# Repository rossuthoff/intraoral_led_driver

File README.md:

# intraoral led driver
Switching boost LED driver based on the Linear Technology [LT3478-1](http://www.analog.com/en/products/power-management/led-driver-ic/buck-boost-led-drivers/lt3478.html) chip. This LED driver is used for the oral cancer screening device described in [1]. 

## related repositories
This design requires the footprints found in the [kicad_footprints](https://github.com/rossuthoff/kicad_footprints) repository. Make sure the library and .mod files are added to your folder search locations. This board utilizes the [ytai/IOIO](https://github.com/ytai/ioio) microcontroller (MCU). Other microcontrollers that can send 3.3 V signals and control an I2C interface may be used. 

## general use
### power supply
LED driver is used in boost mode. The battery voltage must be less than the voltage drop across each individual LED string. Connector J5 supplies power to the MCU.

### led strings
Connect the LED strings to A+/A- and B+/B- connections. The LED string to be illuminated is controlled through a 3.3V signal to the sA or sB pins. The applied current is controlled through a Analog Devices [AD5247](http://www.analog.com/en/products/digital-to-analog-converters/digital-potentiometers/ad5247.html) digital potentiometer with an I2C interface.

# references
[1] Uthoff, R. D. et al. Development of a dual-modality, dual-view smartphone-based imaging system for oral cancer detection. in Proc. SPIE 10486, Design and Quality for Biomedical Technologies XI 10486, 104860V-10486–7 (SPIE, 2018).

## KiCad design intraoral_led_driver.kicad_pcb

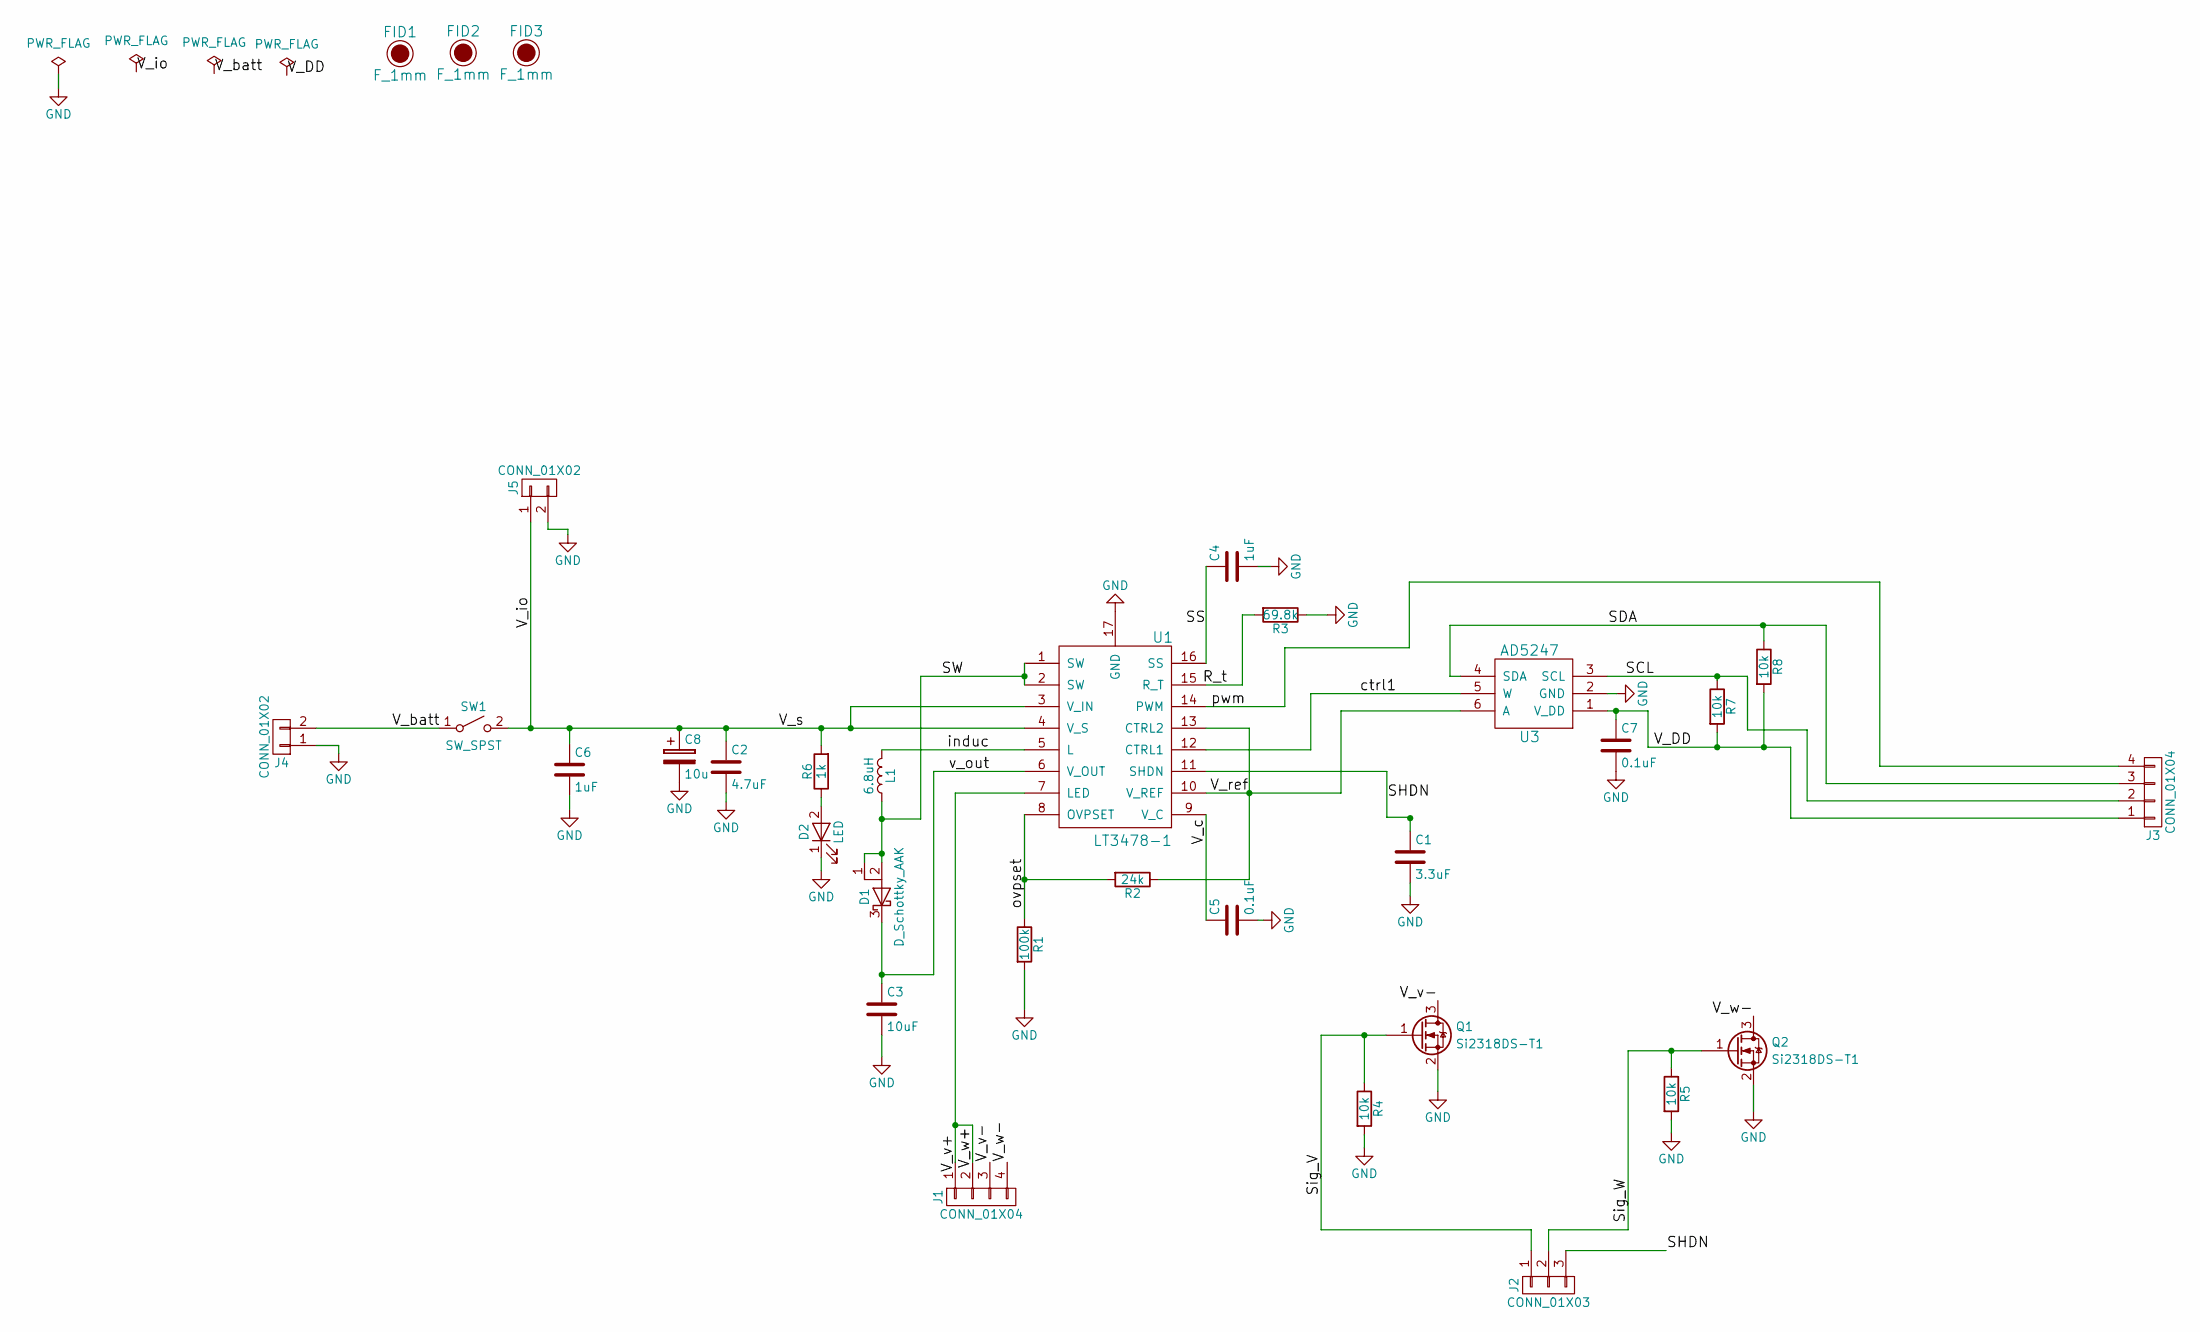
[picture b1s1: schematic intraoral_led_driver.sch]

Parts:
C1: 3.3uF; C_0603
C2: 4.7uF; C_1206
C3: 10uF; C_1812
C4, C6: 1uF; C_0603
C5, C7: 0.1uF; C_0603
C8: 10u; CP_Tantalum_Case-A_EIA-3216-18_Reflow
D1: D_Schottky_AAK; D_PowerDI-5
D2: LED; LED_0603
FID1, FID2, FID3: F_1mm; Fiducial_1mm_Dia_2mm_Outer_CopperTop
J1, J3: CONN_01X04; JST_PH_S4B-PH-SM4-TB_04x2.00mm_Angled
J2: CONN_01X03; JST_PH_S3B-PH-SM4-TB_03x2.00mm_Angled
J4, J5: CONN_01X02; JST_PH_S2B-PH-SM4-TB_02x2.00mm_Angled
L1: 6.8uH; Sumida_L_CDRH105R
Q1, Q2: Si2318DS-T1; SOT-23
R1: 100k; R_0402
R2: 24k; R_0402
R3: 69.8k; R_0402
R4, R5, R7, R8: 10k; R_0603
R6: 1k; R_0603
SW1: SW_SPST; C&K_SPST_switch_L101011MS02Q
U1: LT3478-1; TSSOP-16-1EP_4.4x5mm_Pitch0.65mm
U3: AD5247; SC-70-6

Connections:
/R_t: R3.2, U1.15 (R_T)
/SCL: J3.2, R7.1, U3.3 (SCL)
/SDA: J3.3, R8.1, U3.4 (SDA)
/SHDN: C1.1, J2.3, U1.11 (SHDN)
/SS: C4.1, U1.16 (SS)
/SW: D1.1 (A), D1.2 (A), L1.1, U1.1 (SW), U1.2 (SW)
/Sig_V: J2.1, Q1.1 (G), R4.1
/Sig_W: J2.2, Q2.1 (G), R5.1
/V_DD: C7.1, J3.1, R7.2, R8.2, U3.1 (V_DD)
/V_batt: J4.2, SW1.1 (A)
/V_c: C5.1, U1.9 (V_C)
/V_io: C2.1, C6.1, C8.1, J5.1, R6.2, SW1.2 (B), U1.3 (V_IN), U1.4 (V_S)
/V_ref: R2.1, U1.10 (V_REF), U1.13 (CTRL2), U3.6 (A)
/V_v+: J1.1, J1.2, U1.7 (LED)
/V_v-: J1.3, Q1.3 (D)
/V_w-: J1.4, Q2.3 (D)
/ctrl1: U1.12 (CTRL1), U3.5 (W)
/induc: L1.2, U1.5 (L)
/ovpset: R1.1, R2.2, U1.8 (OVPSET)
/pwm: J3.4, U1.14 (PWM)
/v_out: C3.1, D1.3 (K), U1.6 (V_OUT)
GND: C1.2, C2.2, C3.2, C4.2, C5.2, C6.2, C7.2, C8.2, D2.1 (K), J4.1, J5.2, Q1.2 (S), Q2.2 (S), R1.2, R3.1, R4.2, R5.2, U1.17 (GND), U3.2 (GND)
unnamed: D2.2 (A), R6.1

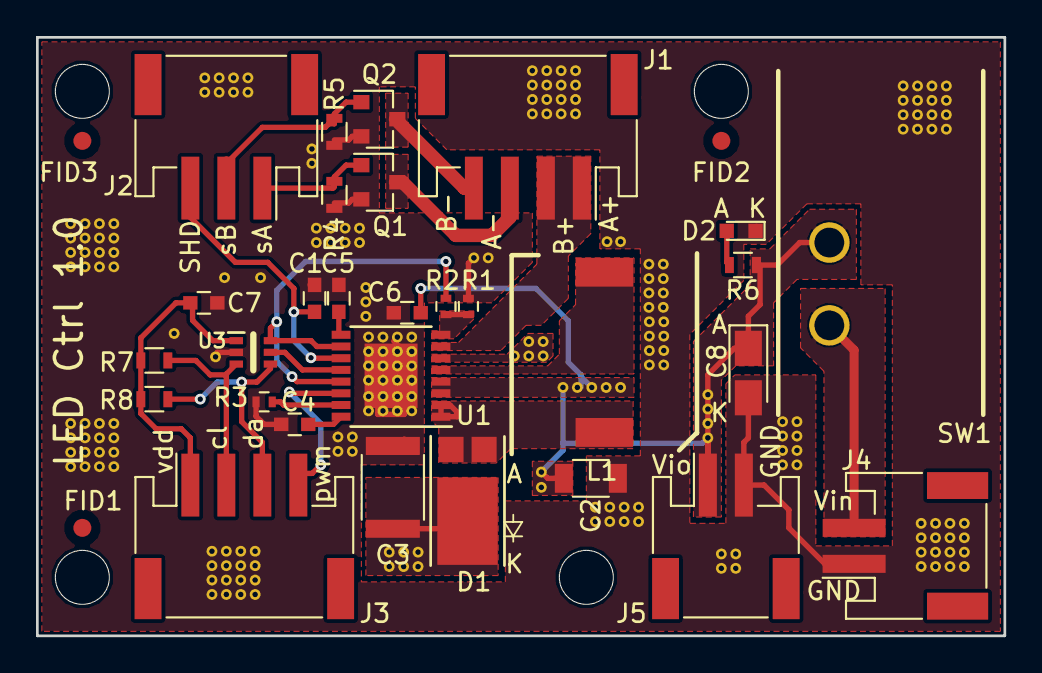
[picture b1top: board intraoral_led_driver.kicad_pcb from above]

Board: 2 copper layers, 53.8 x 33.2 mm, 32 parts (0 on the bottom side), 23 nets.

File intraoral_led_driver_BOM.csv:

Reference,Locations,Value,Footprint,Notes,Manufacturer,PN,Distributor,Dist PN,Dist Link
C1,1,3.3uF,Capacitors_SMD:C_0603,25V,TDK Corporation,C1608X5R1E335K080AC,Digikey,445-14141-1-ND,https://www.digikey.com/product-detail/en/tdk-corporation/C1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
C2,1,4.7uF,Capacitors_SMD:C_1206,25V,TDK Corporation,C3216X5R1E475K160AA,Digikey,445-4047-2-ND,http://www.digikey.com/product-detail/en/tdk-corporation/C32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
C3,1,10uF,Capacitors_SMD:C_1812,25V,TDK Corporation,C4532X5R1E106M250KA,Digikey,445-3926-2-ND,http://www.digikey.com/product-detail/en/tdk-corporation/C45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
"C4, C6",2,1uF,Capacitors_SMD:C_0603,25V,TDK Corporation,CGB3B1X5R1E105K055AC,Digikey,445-13224-2-ND,http://www.digikey.com/product-detail/en/tdk-corporation/CGB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
"C5, C7",2,0.1uF,Capacitors_SMD:C_0603,,TDK Corporation,C1608X8R1E104K080AA,Digikey,445-2500-2-ND,http://www.digikey.com/product-detail/en/tdk-corporation/C16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
C8,1,10uF,Capacitors_Tantalum_SMD:CP_Tantalum_Case-A_EIA-3216-18_Reflow,10V,AVX Corporation,TPSA106K010R1800,Digikey,478-3317-1-ND,https://www.digikey.com/product-detail/en/avx-corporation/TP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
D1,1,D_Schottky_AAK,footprints:D_PowerDI-5,,Diode Incorporated,PDS560-13,Digikey,PDS560DICT-ND,http://www.digikey.com/product-detail/en/diodes-incorporated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
D2,1,LED,footprints:LED_0603,,Panasonic Electric Components,LNJ937W8CRA,Digikey,LNJ937W8CRATR-ND,http://www.digikey.com/product-detail/en/panasonic-electroni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
"J1, J3",2,CONN_01X04,Connectors_JST:JST_PH_S4B-PH-SM4-TB_04x2.00mm_Angled,,JST Sales America,S4B-PH-SM4-TB(LF)(SN),Digikey,455-1751-1-ND,https://www.digikey.com/product-detail/en/jst-sales-america-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
J2,1,CONN_01X03,Connectors_JST:JST_PH_S3B-PH-SM4-TB_03x2.00mm_Angled,,JST Sales America,S3B-PH-SM4-TB(LF)(SN),Digikey,455-1750-2-ND,https://www.digikey.com/product-detail/en/jst-sales-america-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
"J4, J5",2,CONN_01X02,Connectors_JST:JST_PH_S2B-PH-SM4-TB_02x2.00mm_Angled,,JST Sales America,S2B-PH-SM4-TB(LF)(SN),Digikey,455-1749-2-ND,http://www.digikey.com/product-detail/en/jst-sales-america-i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
L1,1,6.8uH,footprints:Sumida_L_CDRH105R,,Sumida America Components,CDRH105RNP-6R8NC,Digikey,308-1927-2-ND,https://www.digikey.com/product-detail/en/sumida-america-com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
"Q1, Q2",2,Si2318DS-T1,TO_SOT_Packages_SMD:SOT-23,,Vishay Siliconix,SI2318DS-T1-E3,Digikey,SI2318DS-T1-E3TR-ND,http://www.digikey.com/product-detail/en/vishay-siliconix/SI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
R1,1,100k,Resistors_SMD:R_0402,1%,Yageo,RC0402FR-07100KL,Digikey,311-100KLRTR-ND,http://www.digikey.com/product-detail/en/yageo/RC0402FR-0710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
R2,1,24k,Resistors_SMD:R_0402,1%,Yageo,RC0402FR-0724KL,Digikey,311-24KLRTR-ND,http://www.digikey.com/product-detail/en/yageo/RC0402FR-0724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
R3,1,69.8k,Resistors_SMD:R_0402,1%,Yageo,RC0402FR-0769K8L,Digikey,YAG3216TR-ND,http://www.digikey.com/product-detail/en/yageo/RC0402FR-0769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
"R4, R5, R7, R8",4,10k,Resistors_SMD:R_0603,1%,Yageo,RC0603FR-0710KL,Digikey,311-10.0KHRTR-ND,https://www.digikey.com/product-detail/en/yageo/RC0603FR-071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
R6,1,1k,Resistors_SMD:R_0603,1%,Yageo,RC0603FR-071KL,Digikey,311-1.00KHRTR-ND,https://www.digikey.com/product-detail/en/yageo/RC0603FR-071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
SW1,1,SW_SPST,footprints:C&K_SPST_switch_L101011MS02Q,,C&K,L101011MS02Q,Digikey,CKC5106-ND,http://www.digikey.com/product-detail/en/c-k/L101011MS02Q/CK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
U1,1,LT3478-1,footprints:TSSOP-16-1EP_4.4x5mm_Pitch0.65mm,,Linear Technologies,LT3478EFE-1#PBF,Digikey,LT3478EFE-1#PBF-ND,http://www.digikey.com/product-detail/en/linear-technology/L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
U3,1,AD5247,footprints:SC-70-6,,Analog Devices,AD5247BKSZ10-RL7,Digikey,AD5247BKSZ10-RL7CT-ND,https://www.digikey.com/product-detail/en/analog-devices-inc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

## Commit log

2018-04-08 update readme with citation. initial commit of design files
2018-04-08 revert version to 1.0 for initial release. remove AOL logo
2018-04-08 Update readme for additional operational information
2018-04-08 project save
2018-04-08 add doi
2018-05-02 update library pointers to remove error
2018-05-02 update for new connector
